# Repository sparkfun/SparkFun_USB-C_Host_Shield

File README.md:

SparkFun USB-C Host Shield
========================================

<p align="center">

</p>

*[SparkFun USB-C Host Shield (DEV-21247)](https://www.sparkfun.com/products/21247)*

This new version of the [USB Host Shield](https://github.com/sparkfun/USB_Host_Shield) updates the USB Type-A connector to a USB-C connector and provides users with the option to power the shield from the `5V` or `VIN` pins. The USB-C female connector also supplies 5V as any normal USB *(downward facing)* port would.

The SparkFun USB Host Shield contains all of the digital logic and analog circuitry necessary to implement a USB peripheral/host controller with your Arduino. This means you could use your Arduino to interface with and control any USB 2.0 compatible device - thumbdrives, digital cameras, Bluetooth dongles, and much more!

A four-wire serial interface is used to communicate with the host controller chip, so the shield connects the Arduino's hardware SPI pins (D10-13) to the MAX3421E. All SPI signals are sent through a hex converter to step them down to 3.3V.

Repository Contents
-------------------

* **[/docs](/docs/)** - Online documentation files
	* [overrides](/docs/overrides/) - Customization files for the GitHub page's product documentation
	* [assets](/docs/assets/) - Folder containing all the file assets used for the product documentation
		* [board_files](/docs/assets/board_files/) - Files for the product design
			* [Eagle design files](/docs/assets/board_files/eagle_files.zip) (.zip)
			* [Schematic](/docs/assets/board_files/schematic.pdf) (.pdf)
			* [Dimensions](/docs/assets/board_files/dimensions.pdf) (.pdf)
		* [component_documentation](/docs/assets/component_documentation/) - Datasheets and manuals for hardware components
		* [img](/docs/assets/img/) - Images for the product documentation
	* [github](/docs/github/) - Files with instructions for filing GitHub issues/pull-requests
* **[/Firmware](/Firmware/)** - Example sketches demonstrating extra peripherals
* **[/Hardware](/Hardware/)** - Eagle design files (.brd, .sch)

Documentation
--------------
* **[Hookup Guide (mkdocs)](http://docs.sparkfun.com/SparkFun_USB-C_Host_Shield/)** - Hookup guide for the USB-C Host Shield hosted by GitHub pages.

*Need to download or print our hookup guide?*

* [Print *(Print to PDF)* from Single-Page View](http://docs.sparkfun.com/SparkFun_USB-C_Host_Shield/print_view)

Product Variants
----------------
* USB-C Host Shield (USB-C variant)
	* [DEV-21247](https://www.sparkfun.com/products/21247)- v1.0, Initial Release
* USB Host Shield
	* [DEV-09947](https://www.sparkfun.com/products/retired/9947)- v2.0, Fixes `GPX` and `RESET` pin connections
	* [DEV-09628](https://www.sparkfun.com/products/retired/9628)- v1.0, Initial Release

Version History
---------------
* [v01](https://github.com/sparkfun/SparkFun_USB-C_Host_Shield/releases/tag/v10) - Initial Release

License Information
-------------------

This product is _**open source**_! 

Please review the LICENSE.md file for license information.

If you have any questions or concerns about licensing, please contact technical support on our [SparkFun forums](https://forum.sparkfun.com/viewforum.php?f=152).

Distributed as-is; no warranty is given.

- Your friends at SparkFun.

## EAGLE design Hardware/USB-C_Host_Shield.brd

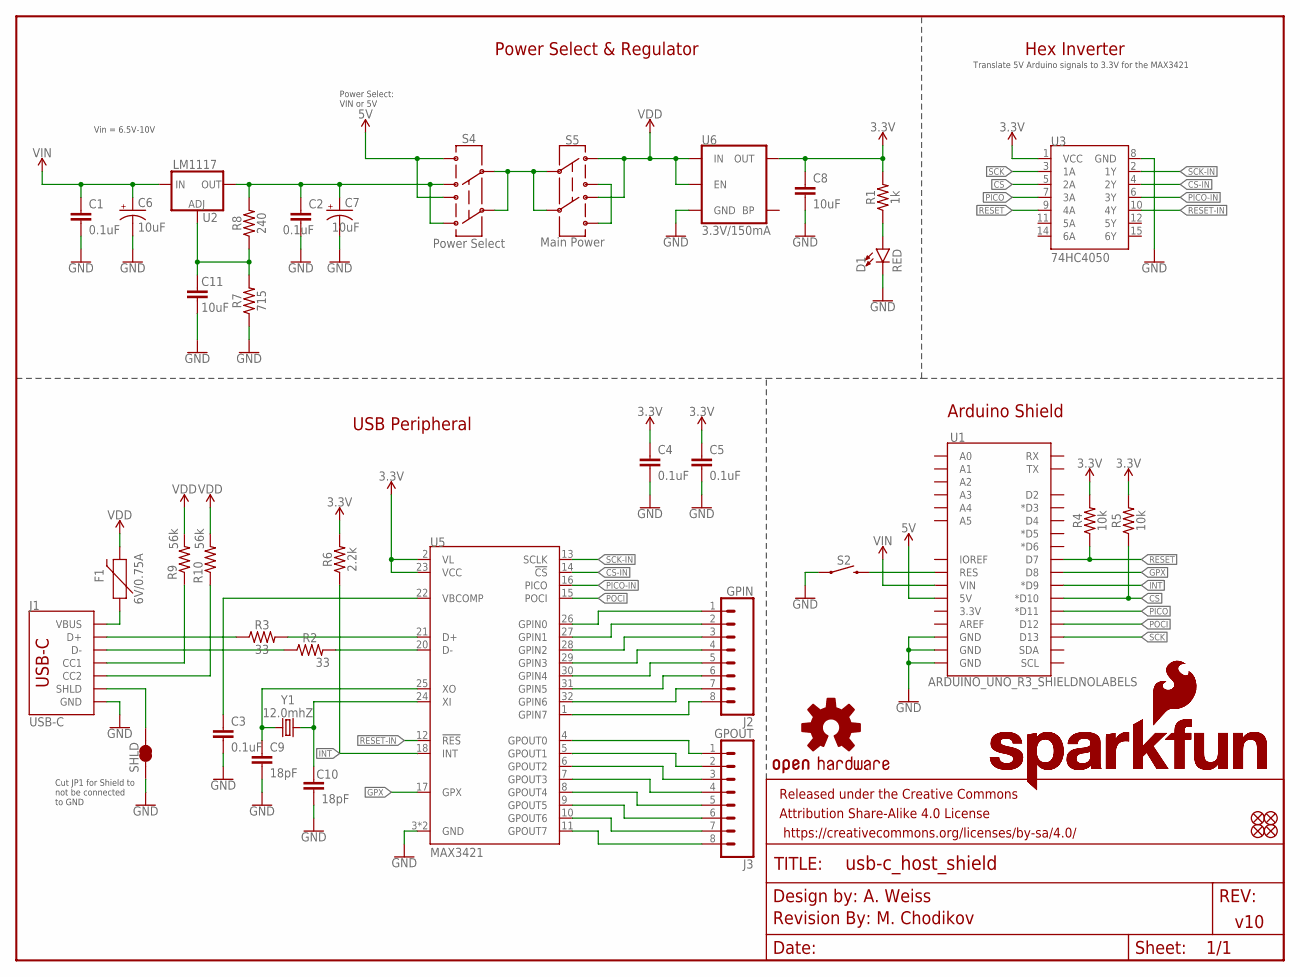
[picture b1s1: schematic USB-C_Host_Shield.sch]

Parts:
C1, C2, C3, C4, C5: 0.1uF; 0603
C6, C7: 10uF; EIA3216
C8: 10uF; 0603
C9, C10: 18pF; 0603
C11: 10uF; 0805
D1: RED; LED-0603
F1: 6V/0.75A; 1206
FD1, FD2, FD3, FD4: FIDUCIALUFIDUCIAL; FIDUCIAL-MICRO
FRAME1: FRAME-LETTER; CREATIVE_COMMONS
J1: USB-C; USB-C-16P-2LAYER-PADS
J2: GPIN; 1X08
J3: GPOUT; 1X08
LOGO1: OSHW-LOGOM; OSHW-LOGO-M
LOGO2: SFE_LOGO_NAME_FLAME.1_INCH; SFE_LOGO_NAME_FLAME_.1
LOGO3: SFE_LOGO_NAME_FLAME.2_INCH; SFE_LOGO_NAME_FLAME_.2
LOGO7: REVISION
R1: 1k; 0603
R2, R3: 33; 0603
R4, R5: 10k; 0603
R6: 2.2k; 0603
R7: 715; 0603
R8: 240; 0603
R9, R10: 56k; 0603
S2: MOMENTARY-SWITCH-SPST-SMD-5.2MM-TALL; TACTILE_SWITCH_SMD_5.2MM
S4: Power Select; SWITCH_DPDT_SMD_AYZ0202
S5: Main Power; SWITCH_DPDT_SMD_AYZ0202
SHLD: JUMPER-SMT_2_NC_TRACE_SILK; SMT-JUMPER_2_NC_TRACE_SILK
U1: ARDUINO_UNO_R3_SHIELDNOLABELS; UNO_R3_SHIELD_NOLABELS
U2: LM1117; SOT223
U3: 74HC4050; SO16
U5: MAX3421; TQFP32
U6: 3.3V/150mA; SOT23-5
Y1: 12.0mhZ; CRYSTAL-SMD-2X2.5MM

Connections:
3.3V: C4.1, C5.1, C8.1, R1.2, R4.2, R5.2, R6.2, U3.1 (VCC), U5.2 (VL), U5.23 (VCC), U6.5 (OUT)
5V: S4.1, S4.4, U1.5V
CC1: J1.A5 (CC1), R9.1
CC2: J1.B5 (CC2), R10.1
CS: R5.1, U1.D10 (*D10), U3.5 (2A)
CS-IN: U3.4 (2Y), U5.14 (!CS)
D_N: J1.A7 (D-), J1.B7 (D-), R2.1
D_P: J1.A6 (D+), J1.B6 (D+), R3.1
GND: C1.2, C2.2, C3.2, C4.2, C5.2, C6.-, C7.-, C8.2, C9.2, C10.2, C11.2, D1.C, J1.GND, J1.GND2 (GND), R7.1, S2.1, SHLD.1, U1.GND@0 (GND), U1.GND@1 (GND), U1.GND@2 (GND), U3.8 (GND), U5.3 (GND), U5.19 (GND), U6.2 (GND)
GPIN0: J2.1, U5.26 (GPIN0)
GPIN1: J2.2, U5.27 (GPIN1)
GPIN2: J2.3, U5.28 (GPIN2)
GPIN3: J2.4, U5.29 (GPIN3)
GPIN4: J2.5, U5.30 (GPIN4)
GPIN5: J2.6, U5.31 (GPIN5)
GPIN6: J2.7, U5.32 (GPIN6)
GPIN7: J2.8, U5.1 (GPIN7)
GPOUT0: J3.1, U5.4 (GPOUT0)
GPOUT1: J3.2, U5.5 (GPOUT1)
GPOUT2: J3.3, U5.6 (GPOUT2)
GPOUT3: J3.4, U5.7 (GPOUT3)
GPOUT4: J3.5, U5.8 (GPOUT4)
GPOUT5: J3.6, U5.9 (GPOUT5)
GPOUT6: J3.7, U5.10 (GPOUT6)
GPOUT7: J3.8, U5.11 (GPOUT7)
GPX: U1.D8, U5.17 (GPX)
INT: R6.1, U1.D9 (*D9), U5.18 (INT)
MAX_D_N: R2.2, U5.20 (D-)
MAX_D_P: R3.2, U5.21 (D+)
unnamed: S2.3 (2), U1.RES
unnamed: S4.2, S4.5, S5.2, S5.5
unnamed: C11.1, R7.2, R8.1, U2.1 (ADJ)
unnamed: S5.1, S5.4
unnamed: C2.1, C7.+, R8.2, S4.3, S4.6, U2.2 (OUT), U2.4 (OUT)
unnamed: D1.A, R1.1
unnamed: J1.SHLD1 (SHLD), J1.SHLD2 (SHLD), J1.SHLD3 (SHLD), J1.SHLD4 (SHLD), SHLD.2
PICO: U1.D11 (*D11), U3.7 (3A)
PICO-IN: U3.6 (3Y), U5.16 (PICO)
POCI: U1.D12, U5.15 (POCI)
RESET: R4.1, U1.D7, U3.9 (4A)
RESET-IN: U3.10 (4Y), U5.12 (!RES)
SCK: U1.D13, U3.3 (1A)
SCK-IN: U3.2 (1Y), U5.13 (SCLK)
VBCOMP: C3.1, U5.22 (VBCOMP)
VBUS: F1.1, J1.VBUS1 (VBUS), J1.VBUS2 (VBUS)
VDD: F1.2, R9.2, R10.2, S5.3, S5.6, U6.1 (IN), U6.3 (EN)
VIN: C1.1, C6.+, U1.VIN, U2.3 (IN)
XI: C10.1, U5.24 (XI), Y1.P3 (2)
XO: C9.1, U5.25 (XO), Y1.P1 (1)

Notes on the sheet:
M. Chodikov
v10
Power Select & Regulator
Arduino Shield
USB Peripheral
Hex Inverter
Translate 5V Arduino signals to 3.3V for the MAX3421
Vin = 6.5V-10V
Cut JP1 for Shield to not be connected to GND
A. Weiss
Power Select: VIN or 5V

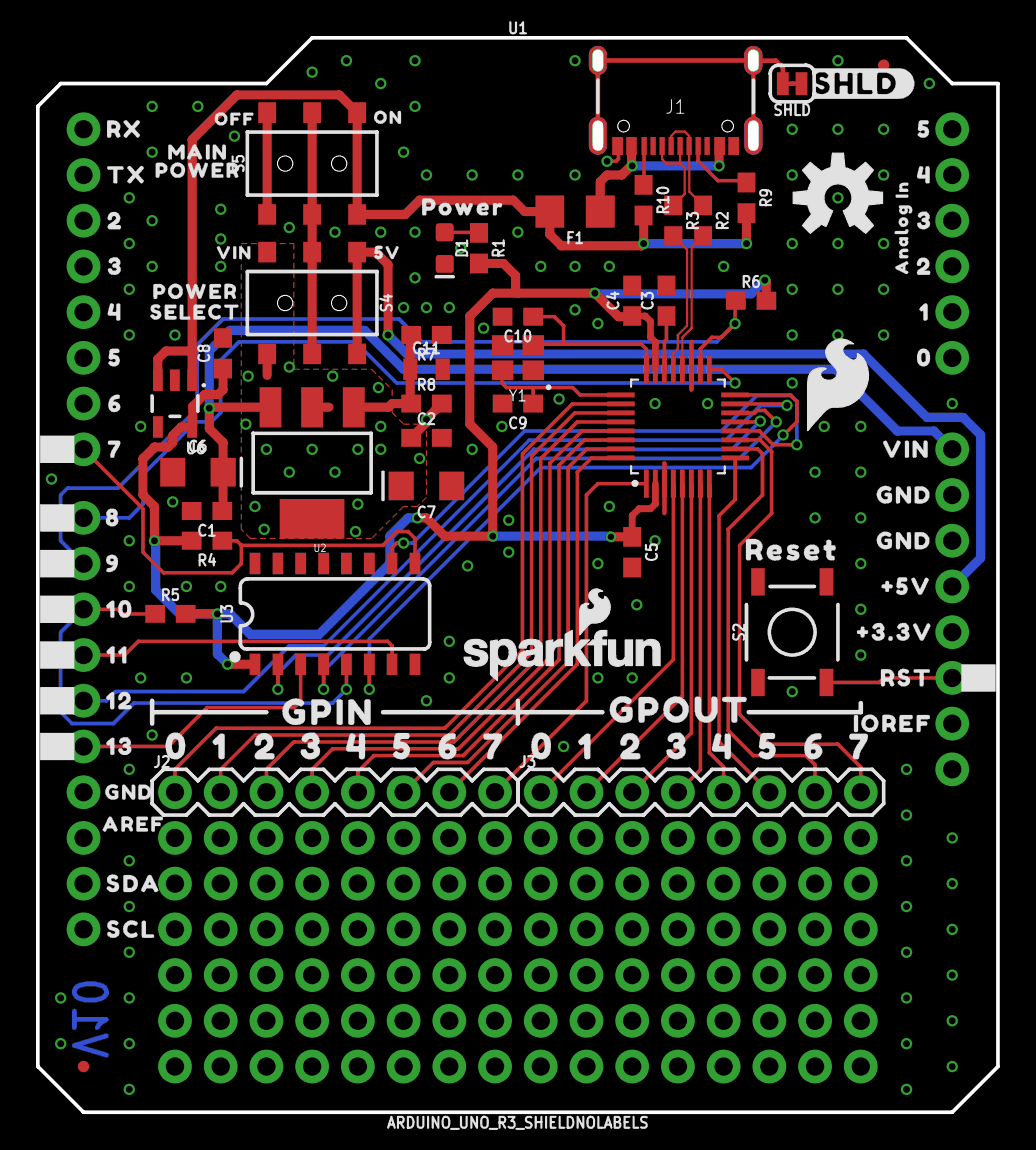
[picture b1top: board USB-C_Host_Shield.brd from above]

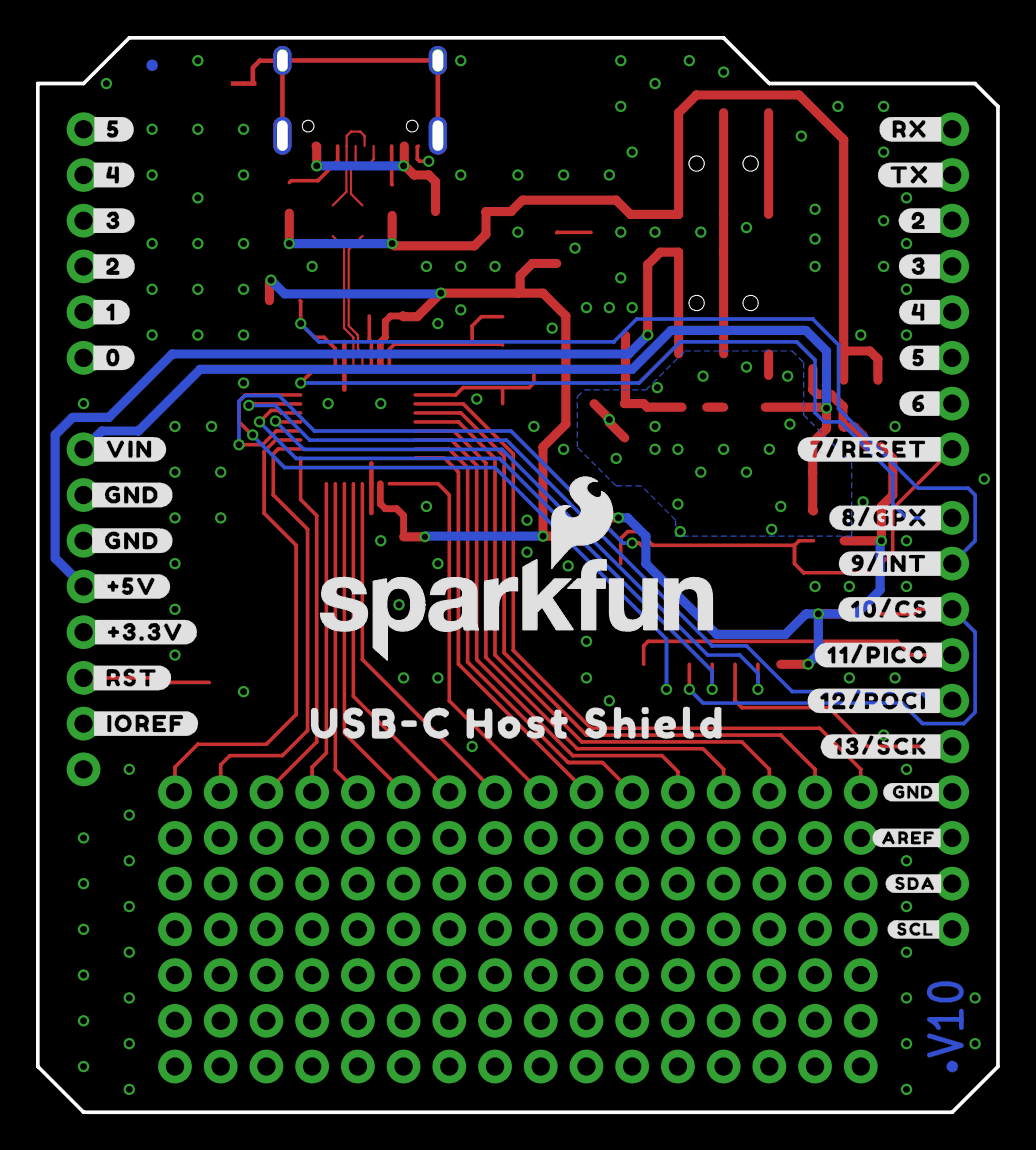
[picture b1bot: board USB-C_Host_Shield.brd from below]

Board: 2 copper layers, 52.9 x 59.3 mm, 139 parts (35 on the bottom side), 49 nets.

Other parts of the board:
U$1: 5V6
U$2: POWER23
U$3: GPIN42
U$4: SFE_LOGO_FLAME_.2
U$5: ON26
U$6: RESET25
U$7: OFF27
U$8: ANALOG_IN28
U$9: USB#C_HOST_SHIELD32
U$10: POWER11
U$11: SHLD#33
U$12: VIN7
U$13: SELECT12
U$14: POWER38
U$15: MAIN40
U$16: GPOUT44
U$17, U$29: 045
U$18, U$30: 146
U$19, U$31: 2147
U$20, U$32: 32148
U$21, U$22: 4332150
U$23, U$25: 54332151
U$24, U$26: 654332152
U$27, U$28: 7654332153
U$33: #5V4
U$34: VIN6
U$35, U$51: GND131211109817654321131211211109876543260
U$36: SDA131211109817654321131211211109876543261
U$37: GND131211211109876543229
U$38, U$55: 21131211211109876543246
U$39, U$56: 321131211211109876543247
U$40, U$57: 4321131211211109876543248
U$41, U$58: 54321131211211109876543249
U$42: 654321131211211109876543250
U$43: 7654321131211211109876543251
U$44: 17654321131211211109876543252
U$45: 017654321131211211109876543253
U$46: 9817654321131211211109876543255
U$47: 109817654321131211211109876543256
U$48: 11109817654321131211211109876543257
U$49: 1211109817654321131211211109876543258
U$50: 131211109817654321131211211109876543259
U$52: AREF131211211109876543230
U$53: SCL131211109817654321131211211109876543262
U$54: IOREF131211109817654321131211211109876543264
U$59: 817654321131211211109876543254
U$60: RST131211109817654321131211211109876543265
U$61: #_4#6
U$62: #3#3V4
U$63: #_5#6
U$64: RX13
U$65: TX1131211211109876543245
U$66: #_3#6
U$67: #_2#6
U$68: #_1#6
U$69: #_0#6
U$70: #_VIN#6
U$71, U$72: #_GND#7
U$73: #_#5V#8
U$74: #_#3#3V#8
U$75: #_RST#8
U$76: #_IOREF#9
U$77: #RX_#10
U$78: #TX_#11
U$79: #2_#12
U$80: #3_#12
U$81: #4_#12
U$82: #5_#12
U$83: #6_#12
U$84: #7#RESET_#12
U$85: #8#GPX_#12
U$86: #9#INT_#12
U$87: #10#CS_#12
U$88: #11#PICO_#12
U$89: #12#POCI_#12
U$90: #13#SCK_#13
U$92: #GND#21
U$93: #SDA#18
U$94: #SCL#19
U$95: #AREF#20

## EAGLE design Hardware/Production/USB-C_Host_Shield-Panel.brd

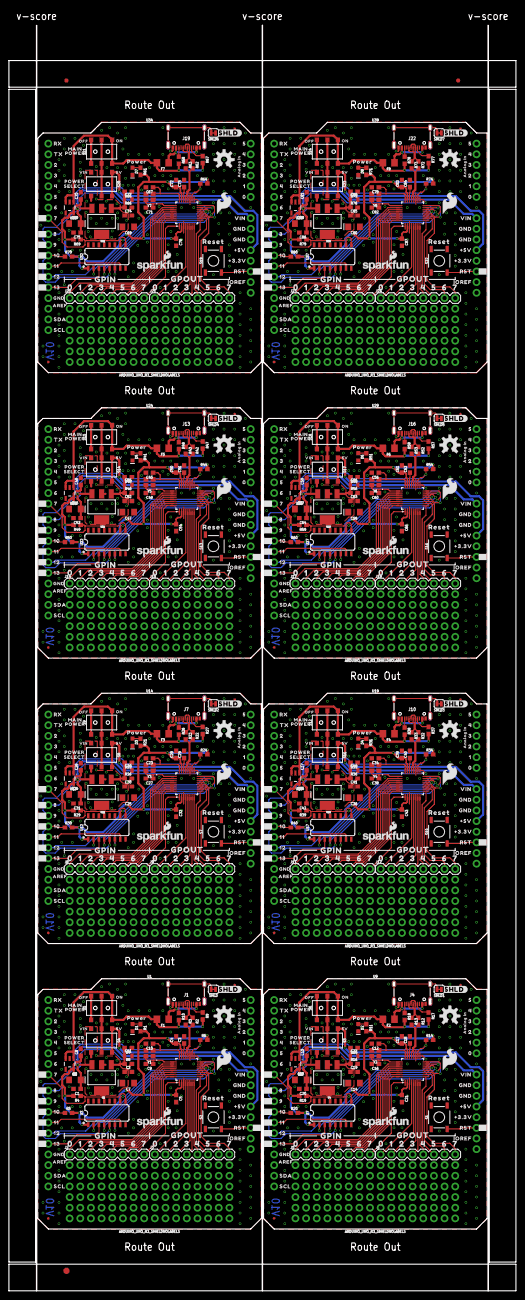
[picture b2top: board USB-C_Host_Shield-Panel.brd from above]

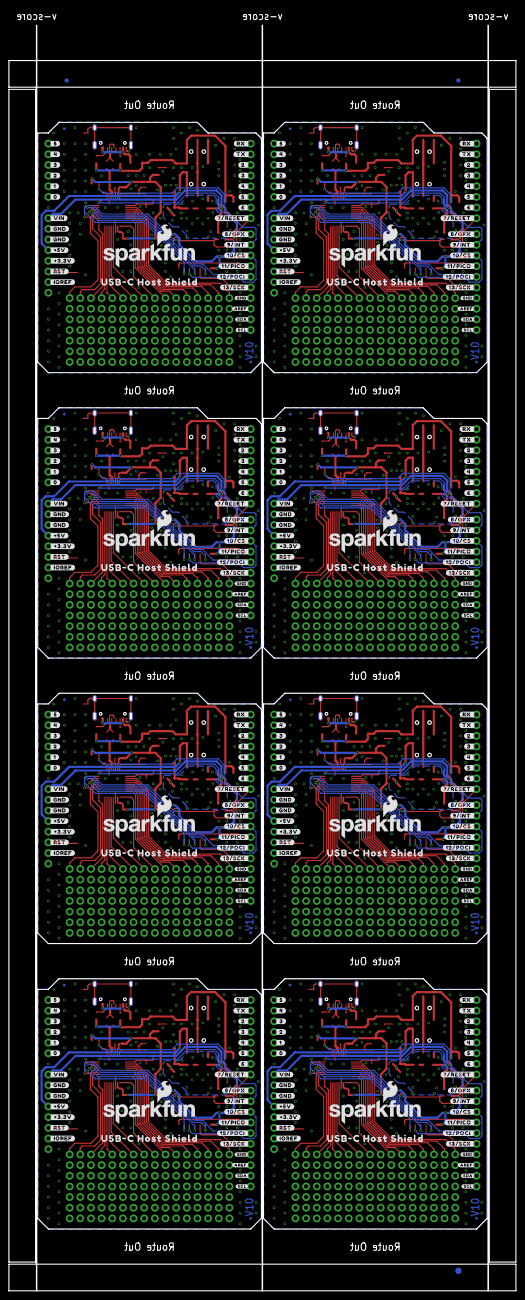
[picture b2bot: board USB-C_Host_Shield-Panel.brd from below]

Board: 2 copper layers, 120.6 x 305.4 mm, 1118 parts (283 on the bottom side), 392 nets.

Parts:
C1, C2, C3, C4, C5, C17, C18, C19, C20, C21, C28, C29, C30, C31, C32, C39, C40, C41, C42, C43, C50, C51, C52, C53, C54, C61, C62, C63, C64, C65, C72, C73, C74, C75, C76, C83, C84, C85, C86, C87: 0.1uF; 0603
C6, C7, C13, C14, C24, C25, C35, C36, C46, C47, C57, C58, C68, C69, C79, C80: 10uF; EIA3216
C8, C15, C26, C37, C48, C59, C70, C81: 10uF; 0603
C9, C10, C12, C16, C23, C27, C34, C38, C45, C49, C56, C60, C67, C71, C78, C82: 18pF; 0603
C11, C22, C33, C44, C55, C66, C77, C88: 10uF; 0805
D1, D2, D3, D4, D5, D6, D7, D8: RED; LED-0603
E$1, E$2, E$3, E$4: FIDUCIAL-1X2
E$5, E$6: FIDUCIAL-1.5X3
F1, F2, F3, F4, F5, F6, F7, F8: 6V/0.75A; 1206
FD1, FD2, FD3, FD4, FD5, FD6, FD7, FD8, FD9, FD10, FD11, FD12, FD13, FD14, FD15, FD16, FD17, FD18, FD19, FD20, FD21, FD22, FD23, FD24, FD25, FD26, FD27, FD28, FD29, FD30, FD31, FD32: FIDUCIALUFIDUCIAL; FIDUCIAL-MICRO
FRAME1, FRAME2, FRAME3, FRAME4, FRAME5, FRAME6, FRAME7, FRAME8: FRAME-LETTER; CREATIVE_COMMONS
J1, J4, J7, J10, J13, J16, J19, J22: USB-C; USB-C-16P-2LAYER-PADS
J2, J5, J8, J11, J14, J17, J20, J23: GPIN; 1X08
J3, J6, J9, J12, J15, J18, J21, J24: GPOUT; 1X08
LOGO1, LOGO4, LOGO9, LOGO13, LOGO17, LOGO21, LOGO25, LOGO29: OSHW-LOGOM; OSHW-LOGO-M
LOGO2, LOGO5, LOGO10, LOGO14, LOGO18, LOGO22, LOGO26, LOGO30: SFE_LOGO_NAME_FLAME.1_INCH; SFE_LOGO_NAME_FLAME_.1
LOGO3, LOGO6, LOGO11, LOGO15, LOGO19, LOGO23, LOGO27, LOGO31: SFE_LOGO_NAME_FLAME.2_INCH; SFE_LOGO_NAME_FLAME_.2
LOGO7, LOGO8, LOGO12, LOGO16, LOGO20, LOGO24, LOGO28, LOGO32: REVISION
R1, R11, R21, R31, R41, R51, R61, R71: 1k; 0603
R2, R3, R12, R13, R22, R23, R32, R33, R42, R43, R52, R53, R62, R63, R72, R73: 33; 0603
R4, R5, R19, R20, R29, R30, R39, R40, R49, R50, R59, R60, R69, R70, R79, R80: 10k; 0603
R6, R14, R24, R34, R44, R54, R64, R74: 2.2k; 0603
R7, R15, R25, R35, R45, R55, R65, R75: 715; 0603
R8, R16, R26, R36, R46, R56, R66, R76: 240; 0603
R9, R10, R17, R18, R27, R28, R37, R38, R47, R48, R57, R58, R67, R68, R77, R78: 56k; 0603
S1, S2, S7, S10, S13, S16, S19, S22: MOMENTARY-SWITCH-SPST-SMD-5.2MM-TALL; TACTILE_SWITCH_SMD_5.2MM
S3, S4, S8, S11, S14, S17, S20, S23: Power Select; SWITCH_DPDT_SMD_AYZ0202
S5, S6, S9, S12, S15, S18, S21, S24: Main Power; SWITCH_DPDT_SMD_AYZ0202
SHLD, SHLD1, SHLD2, SHLD3, SHLD4, SHLD5, SHLD6, SHLD7: JUMPER-SMT_2_NC_TRACE_SILK; SMT-JUMPER_2_NC_TRACE_SILK
U1, U9, U14, U19, U24, U29, U34, U39: ARDUINO_UNO_R3_SHIELDNOLABELS; UNO_R3_SHIELD_NOLABELS
U2, U4, U11, U16, U21, U26, U31, U36: LM1117; SOT223
U3, U7, U12, U17, U22, U27, U32, U37: 74HC4050; SO16
U5, U10, U15, U20, U25, U30, U35, U40: MAX3421; TQFP32
U6, U8, U13, U18, U23, U28, U33, U38: 3.3V/150mA; SOT23-5
U$1, U$123, U$217, U$311, U$405, U$499, U$593, U$687: 5V6
U$2, U$91, U$189, U$283, U$377, U$471, U$565, U$659: POWER23
U$3, U$105, U$199, U$293, U$387, U$481, U$575, U$669: GPIN42
U$4, U$96, U$190, U$284, U$378, U$472, U$566, U$660: SFE_LOGO_FLAME_.2
U$5, U$98, U$192, U$286, U$380, U$474, U$568, U$662: ON26
U$6, U$97, U$191, U$285, U$379, U$473, U$567, U$661: RESET25
U$7, U$99, U$193, U$287, U$381, U$475, U$569, U$663: OFF27
U$8, U$100, U$194, U$288, U$382, U$476, U$570, U$664: ANALOG_IN28
U$9, U$101, U$195, U$289, U$383, U$477, U$571, U$665: USB#C_HOST_SHIELD32
U$10, U$125, U$219, U$313, U$407, U$501, U$595, U$689: POWER11
U$11, U$102, U$196, U$290, U$384, U$478, U$572, U$666: SHLD#33
U$12, U$124, U$218, U$312, U$406, U$500, U$594, U$688: VIN7
U$13, U$126, U$220, U$314, U$408, U$502, U$596, U$690: SELECT12
U$14, U$104, U$198, U$292, U$386, U$480, U$574, U$668: POWER38
U$15, U$103, U$197, U$291, U$385, U$479, U$573, U$667: MAIN40
U$16, U$106, U$200, U$294, U$388, U$482, U$576, U$670: GPOUT44
U$17, U$29, U$107, U$119, U$201, U$213, U$295, U$307, U$389, U$401, U$483, U$495, U$577, U$589, U$671, U$683: 045
U$18, U$30, U$108, U$120, U$202, U$214, U$296, U$308, U$390, U$402, U$484, U$496, U$578, U$590, U$672, U$684: 146
U$19, U$31, U$109, U$121, U$203, U$215, U$297, U$309, U$391, U$403, U$485, U$497, U$579, U$591, U$673, U$685: 2147
U$20, U$32, U$110, U$122, U$204, U$216, U$298, U$310, U$392, U$404, U$486, U$498, U$580, U$592, U$674, U$686: 32148
U$21, U$22, U$111, U$112, U$205, U$206, U$299, U$300, U$393, U$394, U$487, U$488, U$581, U$582, U$675, U$676: 4332150
U$23, U$25, U$113, U$114, U$207, U$208, U$301, U$302, U$395, U$396, U$489, U$490, U$583, U$584, U$677, U$678: 54332151
U$24, U$26, U$115, U$116, U$209, U$210, U$303, U$304, U$397, U$398, U$491, U$492, U$585, U$586, U$679, U$680: 654332152
U$27, U$28, U$117, U$118, U$211, U$212, U$305, U$306, U$399, U$400, U$493, U$494, U$587, U$588, U$681, U$682: 7654332153
U$33, U$156, U$250, U$344, U$438, U$532, U$626, U$720: #5V4
U$34, U$157, U$251, U$345, U$439, U$533, U$627, U$721: VIN6
U$35, U$51, U$149, U$150, U$243, U$244, U$337, U$338, U$431, U$432, U$525, U$526, U$619, U$620, U$713, U$714: GND131211109817654321131211211109876543260
U$36, U$151, U$245, U$339, U$433, U$527, U$621, U$715: SDA131211109817654321131211211109876543261
U$37, U$127, U$221, U$315, U$409, U$503, U$597, U$691: GND131211211109876543229
U$38, U$55, U$131, U$139, U$225, U$233, U$319, U$327, U$413, U$421, U$507, U$515, U$601, U$609, U$695, U$703: 21131211211109876543246
U$39, U$56, U$132, U$140, U$226, U$234, U$320, U$328, U$414, U$422, U$508, U$516, U$602, U$610, U$696, U$704: 321131211211109876543247
U$40, U$57, U$133, U$141, U$227, U$235, U$321, U$329, U$415, U$423, U$509, U$517, U$603, U$611, U$697, U$705: 4321131211211109876543248
U$41, U$58, U$134, U$142, U$228, U$236, U$322, U$330, U$416, U$424, U$510, U$518, U$604, U$612, U$698, U$706: 54321131211211109876543249
U$42, U$135, U$229, U$323, U$417, U$511, U$605, U$699: 654321131211211109876543250
U$43, U$136, U$230, U$324, U$418, U$512, U$606, U$700: 7654321131211211109876543251
U$44, U$137, U$231, U$325, U$419, U$513, U$607, U$701: 17654321131211211109876543252
U$45, U$138, U$232, U$326, U$420, U$514, U$608, U$702: 017654321131211211109876543253
U$46, U$144, U$238, U$332, U$426, U$520, U$614, U$708: 9817654321131211211109876543255
U$47, U$145, U$239, U$333, U$427, U$521, U$615, U$709: 109817654321131211211109876543256
U$48, U$146, U$240, U$334, U$428, U$522, U$616, U$710: 11109817654321131211211109876543257
U$49, U$147, U$241, U$335, U$429, U$523, U$617, U$711: 1211109817654321131211211109876543258
U$50, U$148, U$242, U$336, U$430, U$524, U$618, U$712: 131211109817654321131211211109876543259
U$52, U$128, U$222, U$316, U$410, U$504, U$598, U$692: AREF131211211109876543230
U$53, U$152, U$246, U$340, U$434, U$528, U$622, U$716: SCL131211109817654321131211211109876543262
U$54, U$153, U$247, U$341, U$435, U$529, U$623, U$717: IOREF131211109817654321131211211109876543264
U$59, U$143, U$237, U$331, U$425, U$519, U$613, U$707: 817654321131211211109876543254
U$60, U$154, U$248, U$342, U$436, U$530, U$624, U$718: RST131211109817654321131211211109876543265
U$61, U$159, U$253, U$347, U$441, U$535, U$629, U$723: #_4#6
U$62, U$155, U$249, U$343, U$437, U$531, U$625, U$719: #3#3V4
U$63, U$158, U$252, U$346, U$440, U$534, U$628, U$722: #_5#6
U$64, U$129, U$223, U$317, U$411, U$505, U$599, U$693: RX13
U$65, U$130, U$224, U$318, U$412, U$506, U$600, U$694: TX1131211211109876543245
U$66, U$160, U$254, U$348, U$442, U$536, U$630, U$724: #_3#6
U$67, U$161, U$255, U$349, U$443, U$537, U$631, U$725: #_2#6
U$68, U$162, U$256, U$350, U$444, U$538, U$632, U$726: #_1#6
U$69, U$163, U$257, U$351, U$445, U$539, U$633, U$727: #_0#6
U$70, U$164, U$258, U$352, U$446, U$540, U$634, U$728: #_VIN#6
U$71, U$72, U$165, U$166, U$259, U$260, U$353, U$354, U$447, U$448, U$541, U$542, U$635, U$636, U$729, U$730: #_GND#7
U$73, U$167, U$261, U$355, U$449, U$543, U$637, U$731: #_#5V#8
U$74, U$168, U$262, U$356, U$450, U$544, U$638, U$732: #_#3#3V#8
U$75, U$169, U$263, U$357, U$451, U$545, U$639, U$733: #_RST#8
U$76, U$170, U$264, U$358, U$452, U$546, U$640, U$734: #_IOREF#9
U$77, U$171, U$265, U$359, U$453, U$547, U$641, U$735: #RX_#10
U$78, U$172, U$266, U$360, U$454, U$548, U$642, U$736: #TX_#11
U$79, U$173, U$267, U$361, U$455, U$549, U$643, U$737: #2_#12
U$80, U$174, U$268, U$362, U$456, U$550, U$644, U$738: #3_#12
U$81, U$175, U$269, U$363, U$457, U$551, U$645, U$739: #4_#12
U$82, U$176, U$270, U$364, U$458, U$552, U$646, U$740: #5_#12
U$83, U$177, U$271, U$365, U$459, U$553, U$647, U$741: #6_#12
U$84, U$178, U$272, U$366, U$460, U$554, U$648, U$742: #7#RESET_#12
U$85, U$179, U$273, U$367, U$461, U$555, U$649, U$743: #8#GPX_#12
U$86, U$180, U$274, U$368, U$462, U$556, U$650, U$744: #9#INT_#12
U$87, U$181, U$275, U$369, U$463, U$557, U$651, U$745: #10#CS_#12
U$88, U$182, U$276, U$370, U$464, U$558, U$652, U$746: #11#PICO_#12
U$89, U$183, U$277, U$371, U$465, U$559, U$653, U$747: #12#POCI_#12
U$90, U$184, U$278, U$372, U$466, U$560, U$654, U$748: #13#SCK_#13
U$92, U$188, U$282, U$376, U$470, U$564, U$658, U$752: #GND#21
U$93, U$185, U$279, U$373, U$467, U$561, U$655, U$749: #SDA#18
U$94, U$186, U$280, U$374, U$468, U$562, U$656, U$750: #SCL#19
U$95, U$187, U$281, U$375, U$469, U$563, U$657, U$751: #AREF#20
Y1, Y2, Y3, Y4, Y5, Y6, Y7, Y8: 12.0mhZ; CRYSTAL-SMD-2X2.5MM

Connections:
3.3V: C4.1, C5.1, C8.1, R1.2, R4.2, R5.2, R6.2, U3.1, U5.2, U5.23, U6.5
3.3V1: C15.1, C17.1, C21.1, R11.2, R14.2, R19.2, R20.2, U7.1, U8.5, U10.2, U10.23
3.3V2: C26.1, C28.1, C32.1, R21.2, R24.2, R29.2, R30.2, U12.1, U13.5, U15.2, U15.23
3.3V3: C37.1, C39.1, C43.1, R31.2, R34.2, R39.2, R40.2, U17.1, U18.5, U20.2, U20.23
3.3V4: C48.1, C50.1, C54.1, R41.2, R44.2, R49.2, R50.2, U22.1, U23.5, U25.2, U25.23
3.3V5: C59.1, C61.1, C65.1, R51.2, R54.2, R59.2, R60.2, U27.1, U28.5, U30.2, U30.23
3.3V6: C70.1, C72.1, C76.1, R61.2, R64.2, R69.2, R70.2, U32.1, U33.5, U35.2, U35.23
3.3V7: C81.1, C83.1, C87.1, R71.2, R74.2, R79.2, R80.2, U37.1, U38.5, U40.2, U40.23
5V: S4.1, S4.4, U1.5V
5V1: S3.1, S3.4, U9.5V
5V2: S8.1, S8.4, U14.5V
5V3: S11.1, S11.4, U19.5V
5V4: S14.1, S14.4, U24.5V
5V5: S17.1, S17.4, U29.5V
5V6: S20.1, S20.4, U34.5V
5V7: S23.1, S23.4, U39.5V
CC1: J1.A5, R9.1
CC2: J1.B5, R10.1
CC3: J4.A5, R17.1
CC4: J4.B5, R18.1
CC5: J7.A5, R27.1
CC6: J7.B5, R28.1
CC7: J10.A5, R37.1
CC8: J10.B5, R38.1
CC9: J13.A5, R47.1
CC10: J13.B5, R48.1
CC11: J16.A5, R57.1
CC12: J16.B5, R58.1
CC13: J19.A5, R67.1
CC14: J19.B5, R68.1
CC15: J22.A5, R77.1
CC16: J22.B5, R78.1
CS: R5.1, U1.D10, U3.5
CS1: R20.1, U7.5, U9.D10
CS2: R30.1, U12.5, U14.D10
CS3: R40.1, U17.5, U19.D10
CS4: R50.1, U22.5, U24.D10
CS5: R60.1, U27.5, U29.D10
CS6: R70.1, U32.5, U34.D10
CS7: R80.1, U37.5, U39.D10
CS-IN: U3.4, U5.14
CS-IN1: U7.4, U10.14
CS-IN2: U12.4, U15.14
CS-IN3: U17.4, U20.14
CS-IN4: U22.4, U25.14
CS-IN5: U27.4, U30.14
CS-IN6: U32.4, U35.14
CS-IN7: U37.4, U40.14
D_N: J1.A7, J1.B7, R2.1
D_N1: J4.A7, J4.B7, R12.1
D_N2: J7.A7, J7.B7, R22.1
D_N3: J10.A7, J10.B7, R32.1
D_N4: J13.A7, J13.B7, R42.1
D_N5: J16.A7, J16.B7, R52.1
D_N6: J19.A7, J19.B7, R62.1
D_N7: J22.A7, J22.B7, R72.1
D_P: J1.A6, J1.B6, R3.1
D_P1: J4.A6, J4.B6, R13.1
D_P2: J7.A6, J7.B6, R23.1
D_P3: J10.A6, J10.B6, R33.1
D_P4: J13.A6, J13.B6, R43.1
D_P5: J16.A6, J16.B6, R53.1
D_P6: J19.A6, J19.B6, R63.1
D_P7: J22.A6, J22.B6, R73.1
GND: C1.2, C2.2, C3.2, C4.2, C5.2, C6.-, C7.-, C8.2, C9.2, C10.2, C11.2, D1.C, J1.GND, J1.GND2, R7.1, S2.1, SHLD.1, U1.GND@0, U1.GND@1, U1.GND@2, U3.8, U5.3, U5.19, U6.2
GND1: C12.2, C13.-, C14.-, C15.2, C16.2, C17.2, C18.2, C19.2, C20.2, C21.2, C22.2, D2.C, J4.GND, J4.GND2, R15.1, S1.1, SHLD1.1, U7.8, U8.2, U9.GND@0, U9.GND@1, U9.GND@2, U10.3, U10.19
GND2: C23.2, C24.-, C25.-, C26.2, C27.2, C28.2, C29.2, C30.2, C31.2, C32.2, C33.2, D3.C, J7.GND, J7.GND2, R25.1, S7.1, SHLD2.1, U12.8, U13.2, U14.GND@0, U14.GND@1, U14.GND@2, U15.3, U15.19
GND3: C34.2, C35.-, C36.-, C37.2, C38.2, C39.2, C40.2, C41.2, C42.2, C43.2, C44.2, D4.C, J10.GND, J10.GND2, R35.1, S10.1, SHLD3.1, U17.8, U18.2, U19.GND@0, U19.GND@1, U19.GND@2, U20.3, U20.19
GND4: C45.2, C46.-, C47.-, C48.2, C49.2, C50.2, C51.2, C52.2, C53.2, C54.2, C55.2, D5.C, J13.GND, J13.GND2, R45.1, S13.1, SHLD4.1, U22.8, U23.2, U24.GND@0, U24.GND@1, U24.GND@2, U25.3, U25.19
GND5: C56.2, C57.-, C58.-, C59.2, C60.2, C61.2, C62.2, C63.2, C64.2, C65.2, C66.2, D6.C, J16.GND, J16.GND2, R55.1, S16.1, SHLD5.1, U27.8, U28.2, U29.GND@0, U29.GND@1, U29.GND@2, U30.3, U30.19
GND6: C67.2, C68.-, C69.-, C70.2, C71.2, C72.2, C73.2, C74.2, C75.2, C76.2, C77.2, D7.C, J19.GND, J19.GND2, R65.1, S19.1, SHLD6.1, U32.8, U33.2, U34.GND@0, U34.GND@1, U34.GND@2, U35.3, U35.19
GND7: C78.2, C79.-, C80.-, C81.2, C82.2, C83.2, C84.2, C85.2, C86.2, C87.2, C88.2, D8.C, J22.GND, J22.GND2, R75.1, S22.1, SHLD7.1, U37.8, U38.2, U39.GND@0, U39.GND@1, U39.GND@2, U40.3, U40.19
GPIN0: J2.1, U5.26
GPIN1: J2.2, U5.27
GPIN2: J2.3, U5.28
GPIN3: J2.4, U5.29
GPIN4: J2.5, U5.30
GPIN5: J2.6, U5.31
GPIN6: J2.7, U5.32
GPIN7: J2.8, U5.1
GPIN8: J5.8, U10.1
GPIN9: J5.7, U10.32
GPIN10: J5.6, U10.31
GPIN11: J5.5, U10.30
GPIN12: J5.4, U10.29
GPIN13: J5.3, U10.28
GPIN14: J5.2, U10.27
GPIN15: J5.1, U10.26
GPIN16: J8.8, U15.1
GPIN17: J8.7, U15.32
GPIN18: J8.6, U15.31
GPIN19: J8.5, U15.30
GPIN20: J8.4, U15.29
GPIN21: J8.3, U15.28
GPIN22: J8.2, U15.27
GPIN23: J8.1, U15.26
GPIN24: J11.8, U20.1
GPIN25: J11.7, U20.32
GPIN26: J11.6, U20.31
GPIN27: J11.5, U20.30
GPIN28: J11.4, U20.29
GPIN29: J11.3, U20.28
GPIN30: J11.2, U20.27
GPIN31: J11.1, U20.26
GPIN32: J14.8, U25.1
GPIN33: J14.7, U25.32
GPIN34: J14.6, U25.31
GPIN35: J14.5, U25.30
GPIN36: J14.4, U25.29
GPIN37: J14.3, U25.28
GPIN38: J14.2, U25.27
GPIN39: J14.1, U25.26
GPIN40: J17.8, U30.1
GPIN41: J17.7, U30.32
GPIN42: J17.6, U30.31
GPIN43: J17.5, U30.30
GPIN44: J17.4, U30.29
GPIN45: J17.3, U30.28
GPIN46: J17.2, U30.27
GPIN47: J17.1, U30.26
GPIN48: J20.8, U35.1
GPIN49: J20.7, U35.32
GPIN50: J20.6, U35.31
GPIN51: J20.5, U35.30
GPIN52: J20.4, U35.29
GPIN53: J20.3, U35.28
GPIN54: J20.2, U35.27
GPIN55: J20.1, U35.26
GPIN56: J23.8, U40.1
GPIN57: J23.7, U40.32
GPIN58: J23.6, U40.31
GPIN59: J23.5, U40.30
GPIN60: J23.4, U40.29
GPIN61: J23.3, U40.28
GPIN62: J23.2, U40.27
GPIN63: J23.1, U40.26
GPOUT0: J3.1, U5.4
GPOUT1: J3.2, U5.5
GPOUT2: J3.3, U5.6
GPOUT3: J3.4, U5.7
GPOUT4: J3.5, U5.8
GPOUT5: J3.6, U5.9
GPOUT6: J3.7, U5.10
GPOUT7: J3.8, U5.11
GPOUT8: J6.1, U10.4
GPOUT9: J6.2, U10.5
GPOUT10: J6.3, U10.6
GPOUT11: J6.4, U10.7
GPOUT12: J6.5, U10.8
GPOUT13: J6.6, U10.9
GPOUT14: J6.7, U10.10
GPOUT15: J6.8, U10.11
GPOUT16: J9.1, U15.4
GPOUT17: J9.2, U15.5
GPOUT18: J9.3, U15.6
GPOUT19: J9.4, U15.7
GPOUT20: J9.5, U15.8
GPOUT21: J9.6, U15.9
GPOUT22: J9.7, U15.10
GPOUT23: J9.8, U15.11
GPOUT24: J12.1, U20.4
GPOUT25: J12.2, U20.5
GPOUT26: J12.3, U20.6
GPOUT27: J12.4, U20.7
GPOUT28: J12.5, U20.8
GPOUT29: J12.6, U20.9
GPOUT30: J12.7, U20.10
GPOUT31: J12.8, U20.11
GPOUT32: J15.1, U25.4
GPOUT33: J15.2, U25.5
GPOUT34: J15.3, U25.6
GPOUT35: J15.4, U25.7
GPOUT36: J15.5, U25.8
GPOUT37: J15.6, U25.9
GPOUT38: J15.7, U25.10
GPOUT39: J15.8, U25.11
GPOUT40: J18.1, U30.4
GPOUT41: J18.2, U30.5
GPOUT42: J18.3, U30.6
GPOUT43: J18.4, U30.7
GPOUT44: J18.5, U30.8
GPOUT45: J18.6, U30.9
GPOUT46: J18.7, U30.10
GPOUT47: J18.8, U30.11
GPOUT48: J21.1, U35.4
GPOUT49: J21.2, U35.5
GPOUT50: J21.3, U35.6
GPOUT51: J21.4, U35.7
GPOUT52: J21.5, U35.8
GPOUT53: J21.6, U35.9
GPOUT54: J21.7, U35.10
GPOUT55: J21.8, U35.11
GPOUT56: J24.1, U40.4
GPOUT57: J24.2, U40.5
GPOUT58: J24.3, U40.6
GPOUT59: J24.4, U40.7
GPOUT60: J24.5, U40.8
GPOUT61: J24.6, U40.9
GPOUT62: J24.7, U40.10
GPOUT63: J24.8, U40.11
GPX: U1.D8, U5.17
GPX1: U9.D8, U10.17
GPX2: U14.D8, U15.17
GPX3: U19.D8, U20.17
GPX4: U24.D8, U25.17
GPX5: U29.D8, U30.17
GPX6: U34.D8, U35.17
GPX7: U39.D8, U40.17
INT: R6.1, U1.D9, U5.18
INT1: R14.1, U9.D9, U10.18
INT2: R24.1, U14.D9, U15.18
INT3: R34.1, U19.D9, U20.18
INT4: R44.1, U24.D9, U25.18
INT5: R54.1, U29.D9, U30.18
INT6: R64.1, U34.D9, U35.18
INT7: R74.1, U39.D9, U40.18
MAX_D_N: R2.2, U5.20
MAX_D_N1: R12.2, U10.20
MAX_D_N2: R22.2, U15.20
MAX_D_N3: R32.2, U20.20
MAX_D_N4: R42.2, U25.20
MAX_D_N5: R52.2, U30.20
MAX_D_N6: R62.2, U35.20
MAX_D_N7: R72.2, U40.20
MAX_D_P: R3.2, U5.21
MAX_D_P1: R13.2, U10.21
MAX_D_P2: R23.2, U15.21
MAX_D_P3: R33.2, U20.21
MAX_D_P4: R43.2, U25.21
MAX_D_P5: R53.2, U30.21
MAX_D_P6: R63.2, U35.21
MAX_D_P7: R73.2, U40.21
unnamed: S2.3, U1.RES
unnamed: S4.2, S4.5, S5.2, S5.5
unnamed: C11.1, R7.2, R8.1, U2.1
unnamed: S5.1, S5.4
unnamed: C2.1, C7.+, R8.2, S4.3, S4.6, U2.2, U2.4
unnamed: D1.A, R1.1
unnamed: J1.SHLD1, J1.SHLD2, J1.SHLD3, J1.SHLD4, SHLD.2
unnamed: D2.A, R11.1
unnamed: C22.1, R15.2, R16.1, U4.1
unnamed: S1.3, U9.RES
unnamed: C14.+, C19.1, R16.2, S3.3, S3.6, U4.2, U4.4
unnamed: J4.SHLD1, J4.SHLD2, J4.SHLD3, J4.SHLD4, SHLD1.2
unnamed: S3.2, S3.5, S6.2, S6.5
unnamed: S6.1, S6.4
unnamed: D3.A, R21.1
unnamed: C33.1, R25.2, R26.1, U11.1
unnamed: S7.3, U14.RES
unnamed: C25.+, C30.1, R26.2, S8.3, S8.6, U11.2, U11.4
unnamed: J7.SHLD1, J7.SHLD2, J7.SHLD3, J7.SHLD4, SHLD2.2
unnamed: S8.2, S8.5, S9.2, S9.5
unnamed: S9.1, S9.4
unnamed: D4.A, R31.1
unnamed: C44.1, R35.2, R36.1, U16.1
unnamed: S10.3, U19.RES
unnamed: C36.+, C41.1, R36.2, S11.3, S11.6, U16.2, U16.4
unnamed: J10.SHLD1, J10.SHLD2, J10.SHLD3, J10.SHLD4, SHLD3.2
unnamed: S11.2, S11.5, S12.2, S12.5
unnamed: S12.1, S12.4
unnamed: D5.A, R41.1
unnamed: C55.1, R45.2, R46.1, U21.1
unnamed: S13.3, U24.RES
unnamed: C47.+, C52.1, R46.2, S14.3, S14.6, U21.2, U21.4
unnamed: J13.SHLD1, J13.SHLD2, J13.SHLD3, J13.SHLD4, SHLD4.2
unnamed: S14.2, S14.5, S15.2, S15.5
unnamed: S15.1, S15.4
unnamed: D6.A, R51.1
unnamed: C66.1, R55.2, R56.1, U26.1
unnamed: S16.3, U29.RES
unnamed: C58.+, C63.1, R56.2, S17.3, S17.6, U26.2, U26.4
unnamed: J16.SHLD1, J16.SHLD2, J16.SHLD3, J16.SHLD4, SHLD5.2
unnamed: S17.2, S17.5, S18.2, S18.5
unnamed: S18.1, S18.4
unnamed: D7.A, R61.1
unnamed: C77.1, R65.2, R66.1, U31.1
unnamed: S19.3, U34.RES
unnamed: C69.+, C74.1, R66.2, S20.3, S20.6, U31.2, U31.4
unnamed: J19.SHLD1, J19.SHLD2, J19.SHLD3, J19.SHLD4, SHLD6.2
unnamed: S20.2, S20.5, S21.2, S21.5
unnamed: S21.1, S21.4
unnamed: D8.A, R71.1
unnamed: C88.1, R75.2, R76.1, U36.1
unnamed: S22.3, U39.RES
unnamed: C80.+, C85.1, R76.2, S23.3, S23.6, U36.2, U36.4
unnamed: J22.SHLD1, J22.SHLD2, J22.SHLD3, J22.SHLD4, SHLD7.2
unnamed: S23.2, S23.5, S24.2, S24.5
unnamed: S24.1, S24.4
PICO: U1.D11, U3.7
PICO1: U7.7, U9.D11
PICO2: U12.7, U14.D11
PICO3: U17.7, U19.D11
PICO4: U22.7, U24.D11
PICO5: U27.7, U29.D11
PICO6: U32.7, U34.D11
PICO7: U37.7, U39.D11
PICO-IN: U3.6, U5.16
PICO-IN1: U7.6, U10.16
PICO-IN2: U12.6, U15.16
PICO-IN3: U17.6, U20.16
PICO-IN4: U22.6, U25.16
PICO-IN5: U27.6, U30.16
PICO-IN6: U32.6, U35.16
PICO-IN7: U37.6, U40.16
POCI: U1.D12, U5.15
POCI1: U9.D12, U10.15
POCI2: U14.D12, U15.15
POCI3: U19.D12, U20.15
POCI4: U24.D12, U25.15
POCI5: U29.D12, U30.15
POCI6: U34.D12, U35.15
POCI7: U39.D12, U40.15
RESET: R4.1, U1.D7, U3.9
RESET1: R19.1, U7.9, U9.D7
RESET2: R29.1, U12.9, U14.D7
RESET3: R39.1, U17.9, U19.D7
RESET4: R49.1, U22.9, U24.D7
RESET5: R59.1, U27.9, U29.D7
RESET6: R69.1, U32.9, U34.D7
RESET7: R79.1, U37.9, U39.D7
RESET-IN: U3.10, U5.12
RESET-IN1: U7.10, U10.12
RESET-IN2: U12.10, U15.12
RESET-IN3: U17.10, U20.12
RESET-IN4: U22.10, U25.12
RESET-IN5: U27.10, U30.12
RESET-IN6: U32.10, U35.12
RESET-IN7: U37.10, U40.12
SCK: U1.D13, U3.3
SCK1: U7.3, U9.D13
SCK2: U12.3, U14.D13
SCK3: U17.3, U19.D13
SCK4: U22.3, U24.D13
SCK5: U27.3, U29.D13
SCK6: U32.3, U34.D13
SCK7: U37.3, U39.D13
SCK-IN: U3.2, U5.13
SCK-IN1: U7.2, U10.13
SCK-IN2: U12.2, U15.13
SCK-IN3: U17.2, U20.13
SCK-IN4: U22.2, U25.13
SCK-IN5: U27.2, U30.13
SCK-IN6: U32.2, U35.13
SCK-IN7: U37.2, U40.13
VBCOMP: C3.1, U5.22
VBCOMP1: C18.1, U10.22
VBCOMP2: C29.1, U15.22
VBCOMP3: C40.1, U20.22
VBCOMP4: C51.1, U25.22
VBCOMP5: C62.1, U30.22
VBCOMP6: C73.1, U35.22
VBCOMP7: C84.1, U40.22
VBUS: F1.1, J1.VBUS1, J1.VBUS2
VBUS1: F2.1, J4.VBUS1, J4.VBUS2
VBUS2: F3.1, J7.VBUS1, J7.VBUS2
VBUS3: F4.1, J10.VBUS1, J10.VBUS2
VBUS4: F5.1, J13.VBUS1, J13.VBUS2
VBUS5: F6.1, J16.VBUS1, J16.VBUS2
VBUS6: F7.1, J19.VBUS1, J19.VBUS2
VBUS7: F8.1, J22.VBUS1, J22.VBUS2
VDD: F1.2, R9.2, R10.2, S5.3, S5.6, U6.1, U6.3
VDD1: F2.2, R17.2, R18.2, S6.3, S6.6, U8.1, U8.3
VDD2: F3.2, R27.2, R28.2, S9.3, S9.6, U13.1, U13.3
VDD3: F4.2, R37.2, R38.2, S12.3, S12.6, U18.1, U18.3
VDD4: F5.2, R47.2, R48.2, S15.3, S15.6, U23.1, U23.3
VDD5: F6.2, R57.2, R58.2, S18.3, S18.6, U28.1, U28.3
VDD6: F7.2, R67.2, R68.2, S21.3, S21.6, U33.1, U33.3
VDD7: F8.2, R77.2, R78.2, S24.3, S24.6, U38.1, U38.3
VIN: C1.1, C6.+, U1.VIN, U2.3
VIN1: C13.+, C20.1, U4.3, U9.VIN
VIN2: C24.+, C31.1, U11.3, U14.VIN
VIN3: C35.+, C42.1, U16.3, U19.VIN
VIN4: C46.+, C53.1, U21.3, U24.VIN
VIN5: C57.+, C64.1, U26.3, U29.VIN
VIN6: C68.+, C75.1, U31.3, U34.VIN
VIN7: C79.+, C86.1, U36.3, U39.VIN
XI: C10.1, U5.24, Y1.P3
XI1: C12.1, U10.24, Y2.P3
XI2: C23.1, U15.24, Y3.P3
XI3: C34.1, U20.24, Y4.P3
XI4: C45.1, U25.24, Y5.P3
XI5: C56.1, U30.24, Y6.P3
XI6: C67.1, U35.24, Y7.P3
XI7: C78.1, U40.24, Y8.P3
XO: C9.1, U5.25, Y1.P1
XO1: C16.1, U10.25, Y2.P1
XO2: C27.1, U15.25, Y3.P1
XO3: C38.1, U20.25, Y4.P1
XO4: C49.1, U25.25, Y5.P1
XO5: C60.1, U30.25, Y6.P1
XO6: C71.1, U35.25, Y7.P1
XO7: C82.1, U40.25, Y8.P1

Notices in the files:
README.md:
License: CC BY-SA 4.0
parts and their libraries:
SparkFun-Capacitors: Licensing: Creative Commons ShareAlike 4.0 International - https://creativecommons.org/licenses/by-sa/4.0
SparkFun-Aesthetics: Released under the Creative Commons Attribution Share-Alike 4.0 License
SparkFun-Aesthetics: https://creativecommons.org/licenses/by-sa/4.0
